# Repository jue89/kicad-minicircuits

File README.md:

# Evaluation boards for Mini-Circuits parts

Some parts from [Mini-Circuits®](http://www.minicircuits.com) brought onto two-sided PCBs with 1mm FR4 core and 35µm copper.

## Cloning

```
git clone --recursive https://github.com/jue89/kicad-minicircuits.git
cd kicad-minicircuits
./setup.sh
```

## Generating Gerber files

I found a little python script for plotting Gerber files in the KiCad repository (demos/python\_scripts\_examples). It will be called by the plot Bash script

```
./plot.sh
```

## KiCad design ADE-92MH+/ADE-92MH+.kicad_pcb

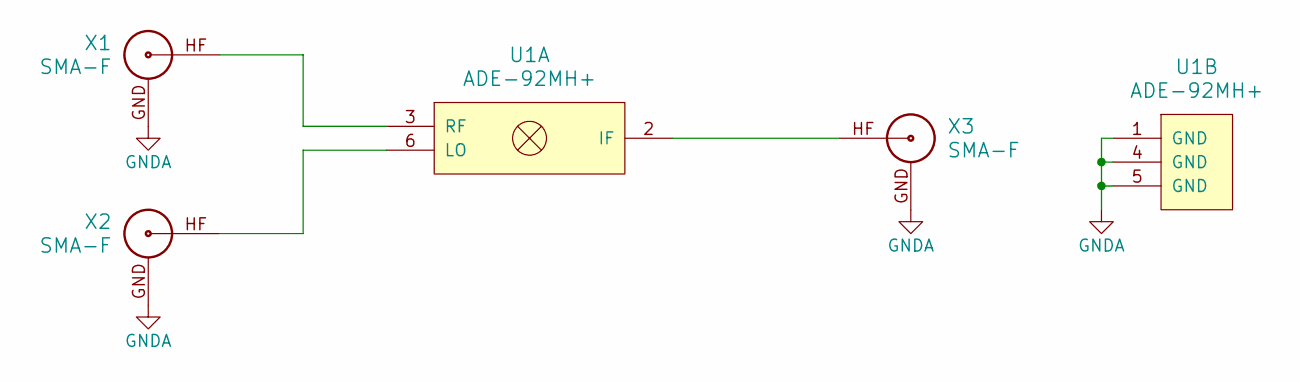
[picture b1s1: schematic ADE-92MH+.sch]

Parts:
U1: ADE-92MH+; CD636
X1, X2, X3: SMA-F; SMA-F-THT

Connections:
GNDA: U1.1 (GND), U1.4 (GND), U1.5 (GND), X1.GND, X2.GND, X3.GND
unnamed: U1.2 (IF), X3.HF
unnamed: U1.3 (RF), X1.HF
unnamed: U1.6 (LO), X2.HF

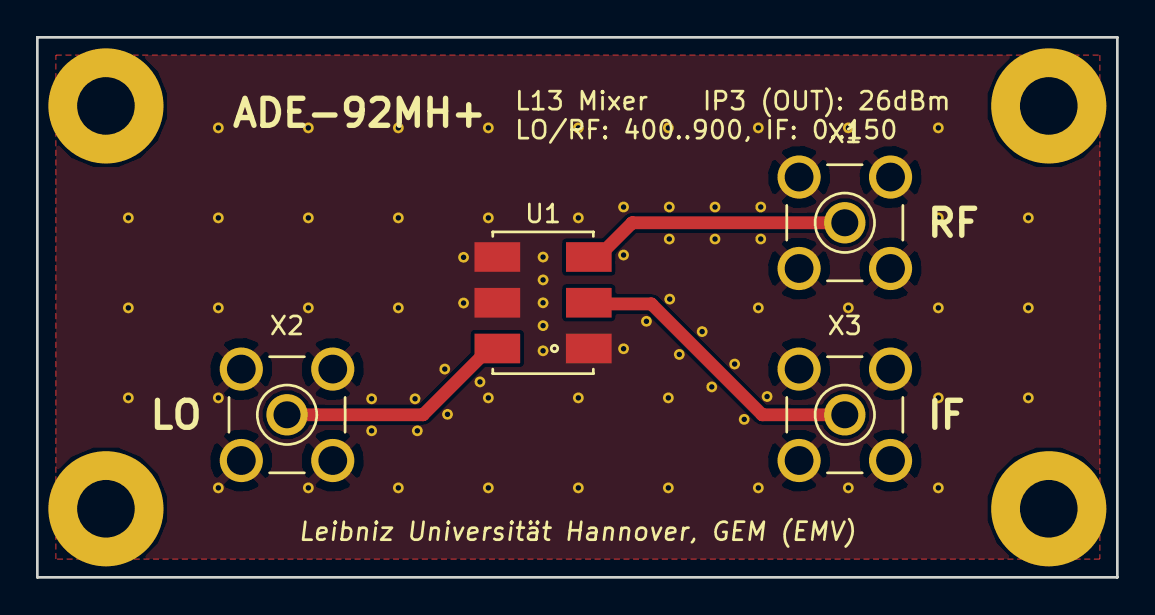
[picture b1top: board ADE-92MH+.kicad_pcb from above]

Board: 2 copper layers, 60.0 x 30.0 mm, 4 parts (0 on the bottom side), 4 nets.

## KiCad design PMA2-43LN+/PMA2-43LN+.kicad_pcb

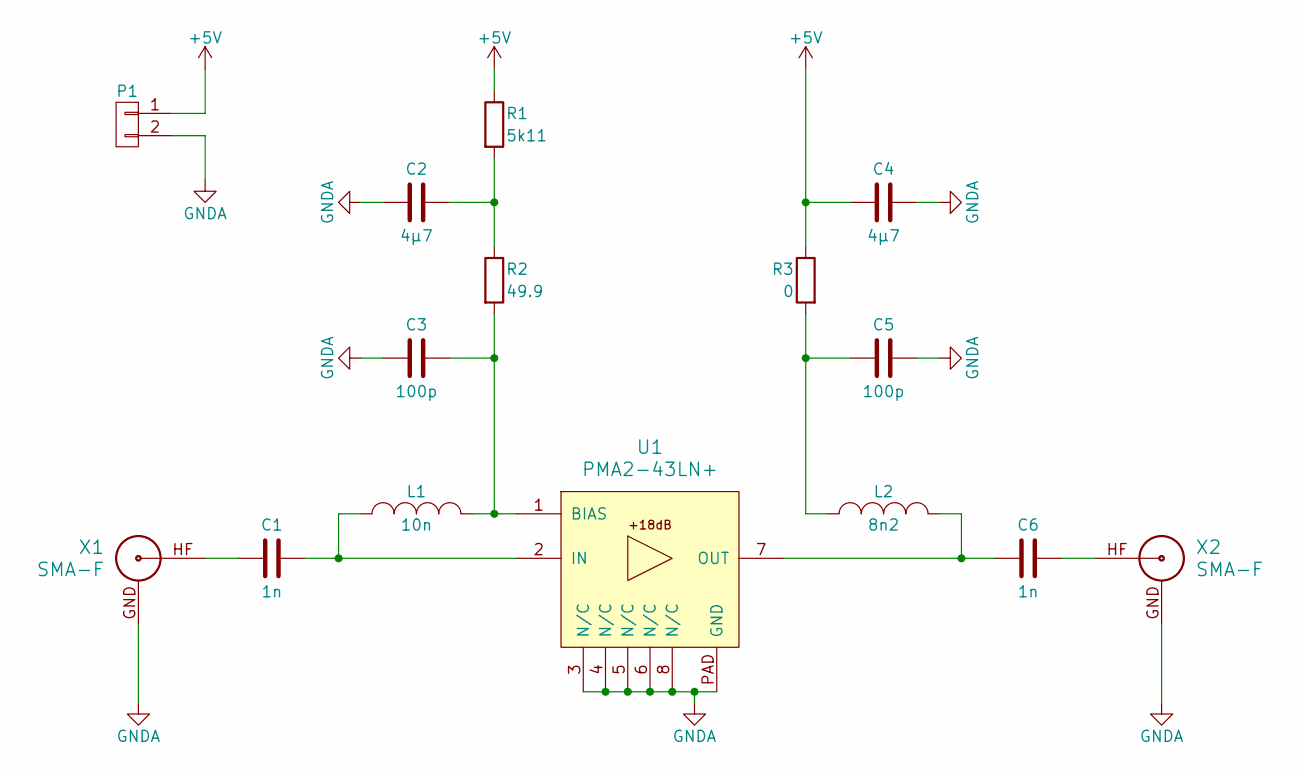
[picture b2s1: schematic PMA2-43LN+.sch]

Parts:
C1, C6: 1n; C_0805
C2, C4: 4µ7; C_0805
C3, C5: 100p; C_0805
L1: 10n; Neosid_Inductor_SM-NE29_SMD1008
L2: 8n2; Neosid_Inductor_SM-NE29_SMD1008
P1: CONN_01X02; Pin_Header_Straight_1x02
R1: 5k11; R_0805
R2: 49.9; R_0805
R3: 0; R_0805
U1: PMA2-43LN+; MC1631
X1, X2: SMA-F; SMA-F-THT

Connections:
+5V: C4.2, P1.1, R1.1, R3.1
GNDA: C2.2, C3.2, C4.1, C5.1, P1.2, U1.3 (N/C), U1.4 (N/C), U1.5 (N/C), U1.6 (N/C), U1.8 (N/C), U1.PAD (GND), X1.GND, X2.GND
unnamed: C1.1, L1.1, U1.2 (IN)
unnamed: C1.2, X1.HF
unnamed: C2.1, R1.2, R2.1
unnamed: C3.1, L1.2, R2.2, U1.1 (BIAS)
unnamed: C5.2, L2.1, R3.2
unnamed: C6.1, X2.HF
unnamed: C6.2, L2.2, U1.7 (OUT)

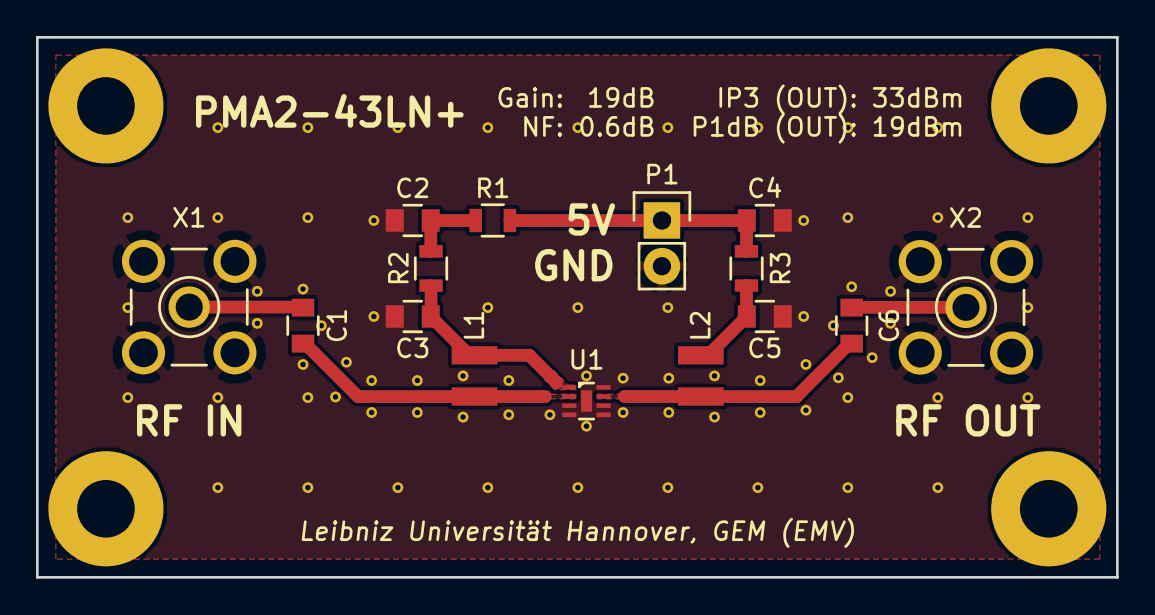
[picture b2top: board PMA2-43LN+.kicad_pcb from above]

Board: 2 copper layers, 60.0 x 30.0 mm, 15 parts (0 on the bottom side), 9 nets.

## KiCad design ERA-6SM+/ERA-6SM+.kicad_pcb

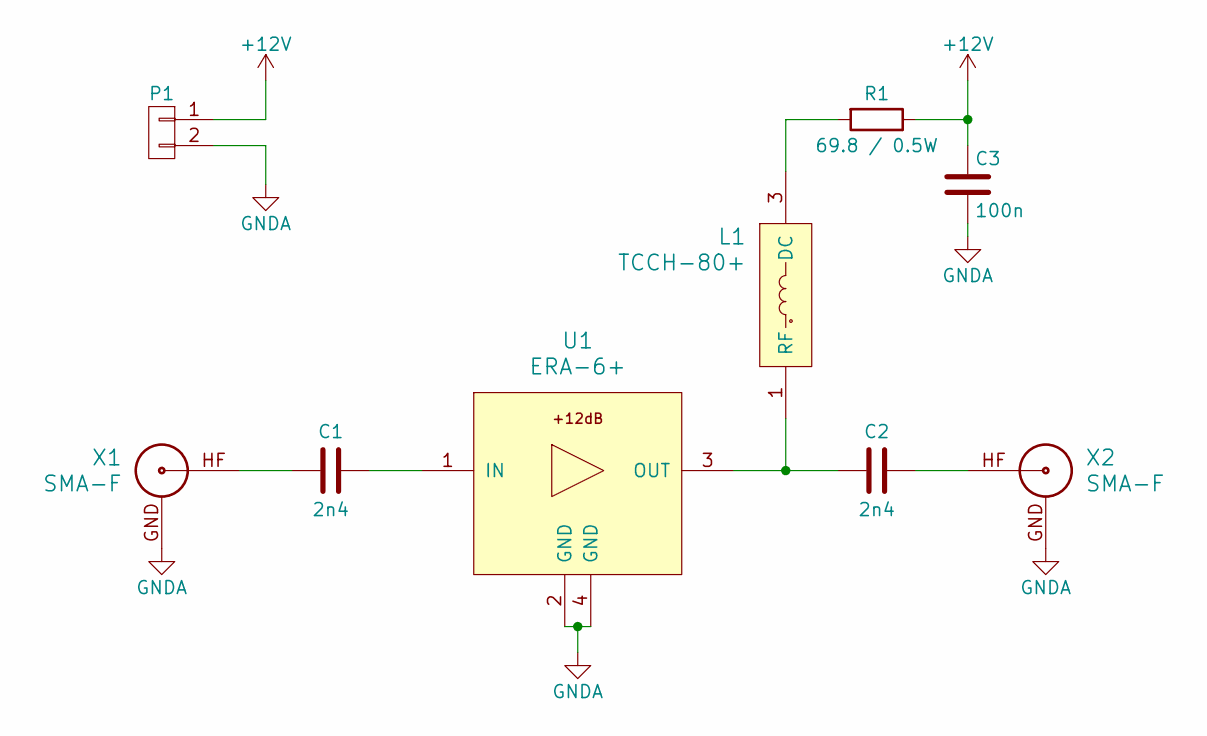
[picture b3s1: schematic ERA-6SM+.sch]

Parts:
C1, C2: 2n4; C_0805
C3: 100n; C_0805
L1: TCCH-80+; GU1604
P1: CONN_01X02; Pin_Header_Straight_1x02
R1: 69.8 / 0.5W; R_1206
U1: ERA-6+; WW107
X1, X2: SMA-F; SMA-F-THT

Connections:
+12V: C3.1, P1.1, R1.1
GNDA: C3.2, P1.2, U1.2 (GND), U1.4 (GND), X1.GND, X2.GND
unnamed: C1.1, U1.1 (IN)
unnamed: C1.2, X1.HF
unnamed: C2.1, X2.HF
unnamed: C2.2, L1.1 (RF), U1.3 (OUT)
unnamed: L1.3 (DC), R1.2

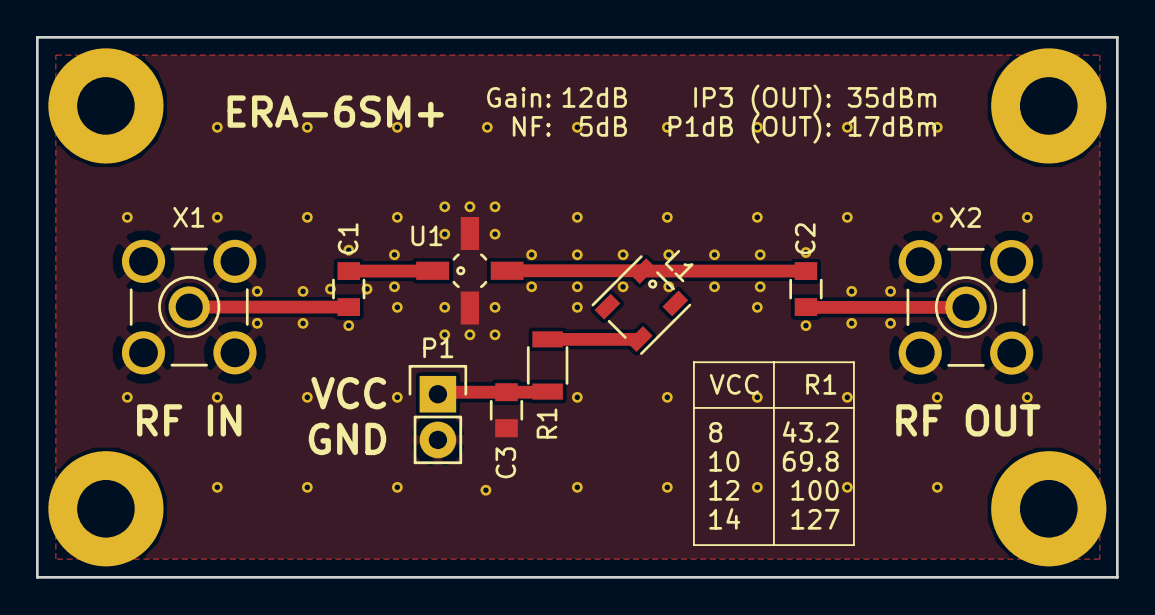
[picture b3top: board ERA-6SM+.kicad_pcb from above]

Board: 2 copper layers, 60.0 x 30.0 mm, 9 parts (0 on the bottom side), 7 nets.

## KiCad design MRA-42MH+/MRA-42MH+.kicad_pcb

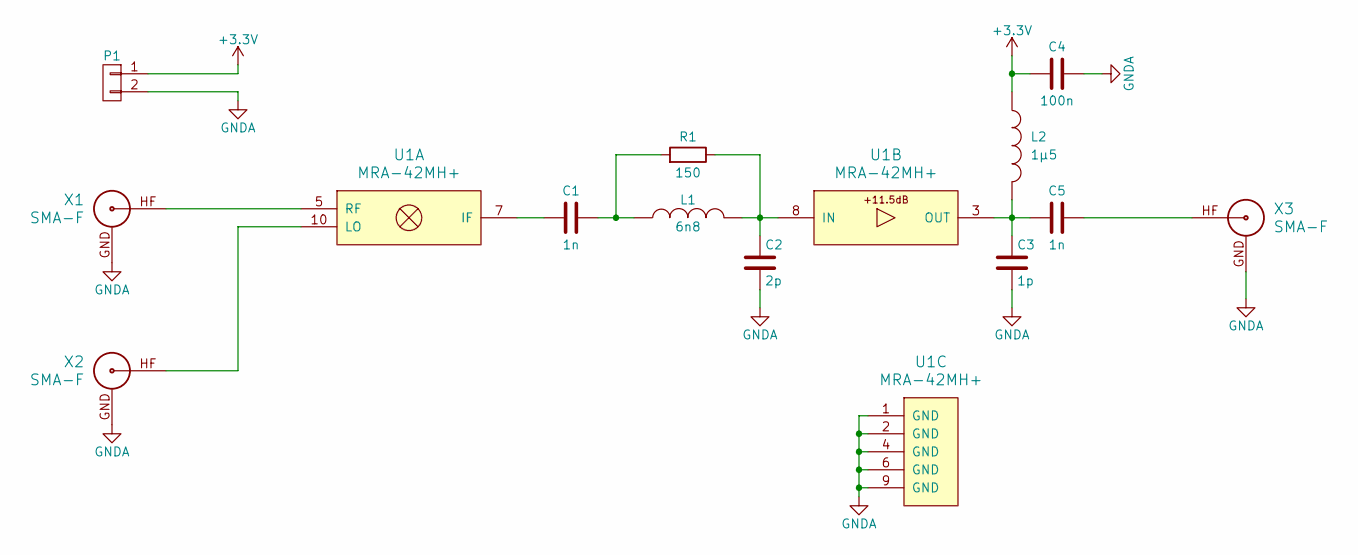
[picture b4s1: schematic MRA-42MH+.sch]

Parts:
C1, C5: 1n; C_0805
C2: 2p; C_0805
C3: 1p; C_0805
C4: 100n; C_0805
L1: 6n8; Neosid_Inductor_SM-NE29_SMD1008
L2: 1µ5; Neosid_Inductor_SM-NE29_SMD1008
P1: CONN_01X02; Pin_Header_Straight_1x02
R1: 150; R_0805
U1: MRA-42MH+; DZ1650
X1, X2, X3: SMA-F; SMA-F-THT

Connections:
+3V3: C4.2, L2.1, P1.1
GNDA: C2.2, C3.2, C4.1, P1.2, U1.1 (GND), U1.2 (GND), U1.4 (GND), U1.6 (GND), U1.9 (GND), X1.GND, X2.GND, X3.GND
unnamed: C1.1, L1.1, R1.2
unnamed: C1.2, U1.7 (IF)
unnamed: C2.1, L1.2, R1.1, U1.8 (IN)
unnamed: C3.1, C5.2, L2.2, U1.3 (OUT)
unnamed: C5.1, X3.HF
unnamed: U1.5 (RF), X1.HF
unnamed: U1.10 (LO), X2.HF

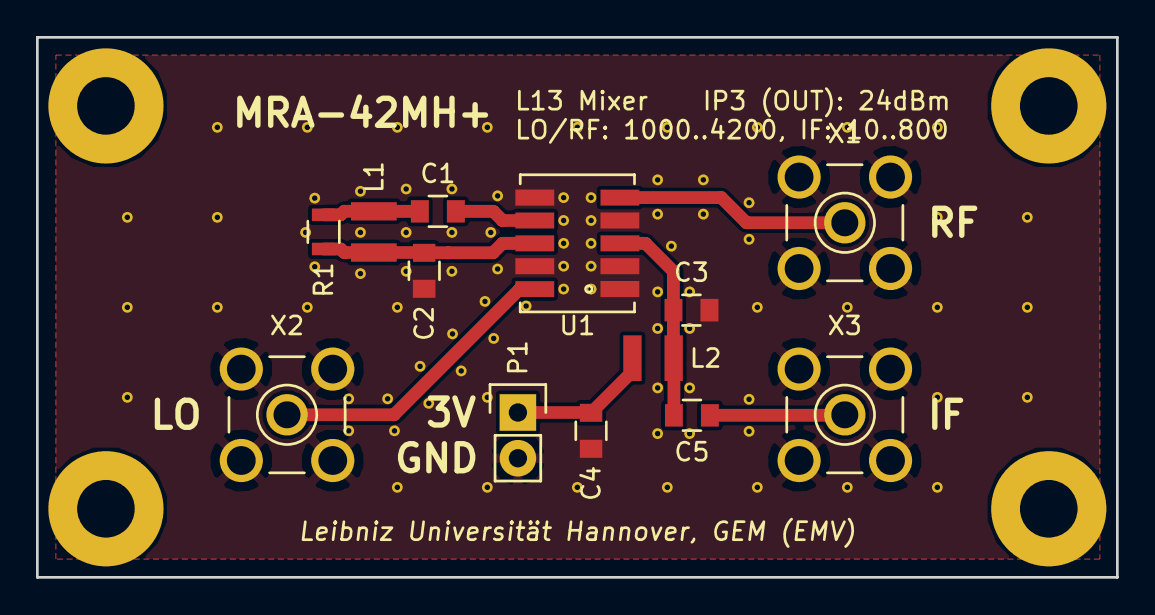
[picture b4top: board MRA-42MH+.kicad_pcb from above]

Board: 2 copper layers, 60.0 x 30.0 mm, 13 parts (0 on the bottom side), 9 nets.

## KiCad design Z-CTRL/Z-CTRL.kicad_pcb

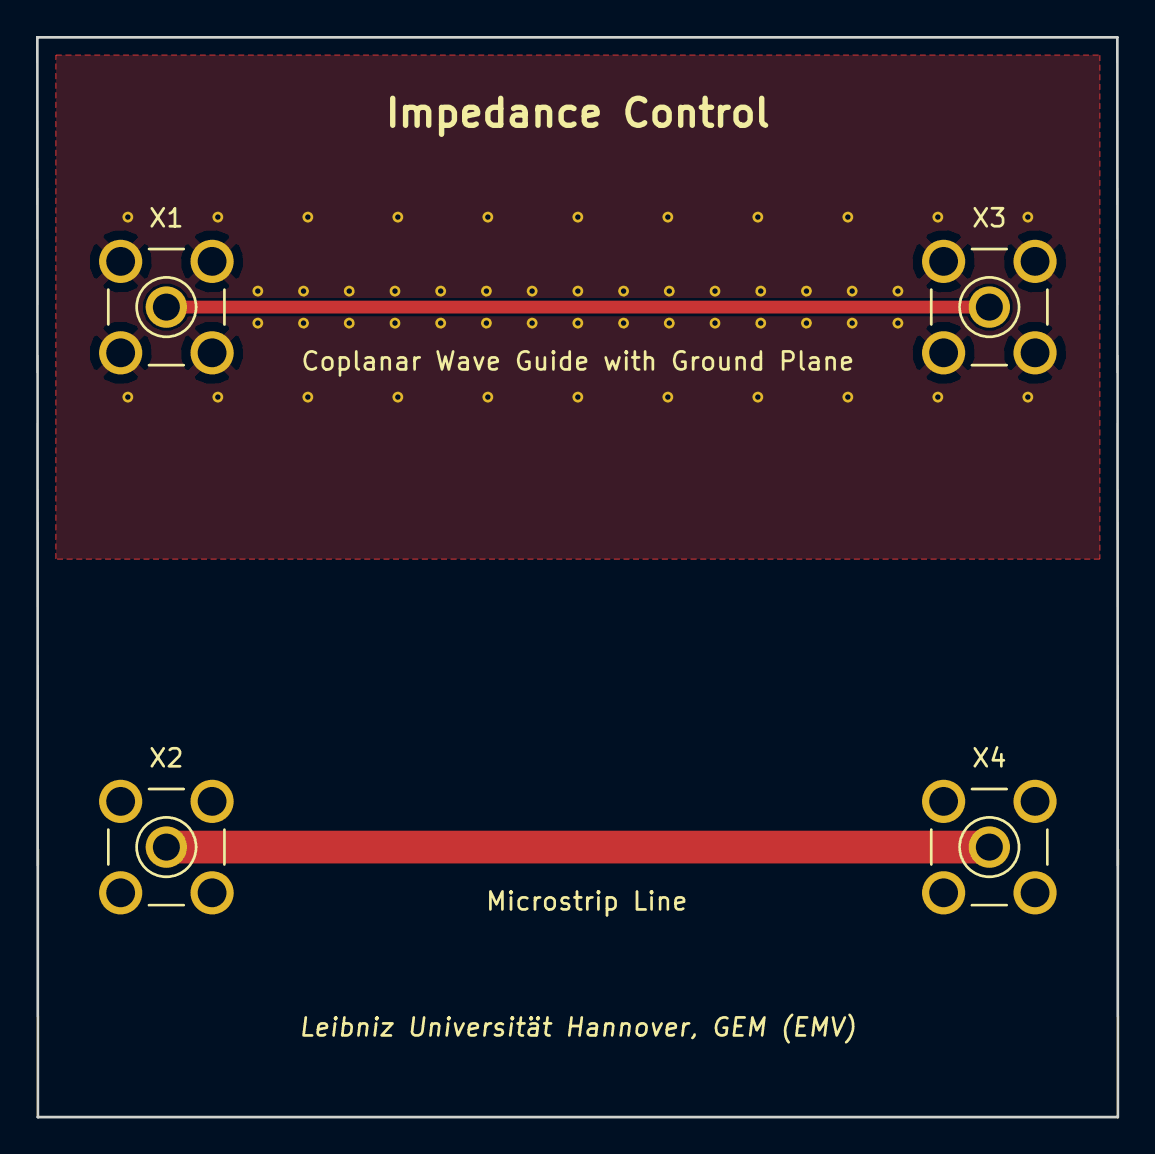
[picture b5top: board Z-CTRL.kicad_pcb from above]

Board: 2 copper layers, 60.0 x 60.0 mm, 4 parts (0 on the bottom side), 4 nets.

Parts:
X1, X2, X3, X4: SMA-F; SMA-F-THT

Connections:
unnamed: X1.GND, X3.GND
unnamed: X1.HF, X3.HF
unnamed: X2.GND, X4.GND
unnamed: X2.HF, X4.HF

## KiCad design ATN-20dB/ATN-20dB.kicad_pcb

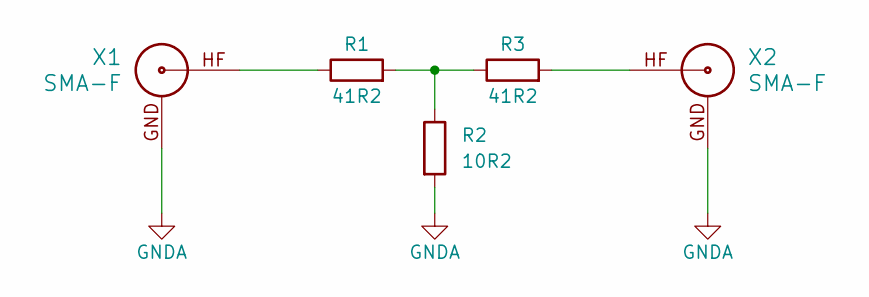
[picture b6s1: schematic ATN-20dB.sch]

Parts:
R1, R3: 41R2; R_0805
R2: 10R2; R_0805
X1, X2: SMA-F; SMA-F-THT

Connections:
GNDA: R2.2, X1.GND, X2.GND
unnamed: R1.1, X1.HF
unnamed: R1.2, R2.1, R3.1
unnamed: R3.2, X2.HF

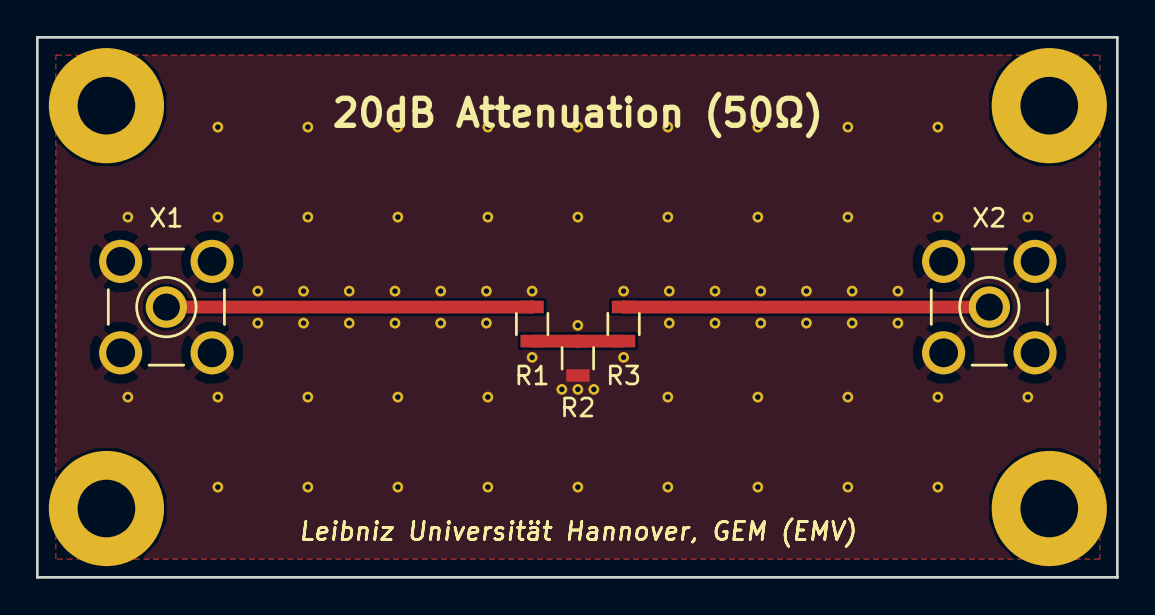
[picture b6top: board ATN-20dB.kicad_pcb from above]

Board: 2 copper layers, 60.0 x 30.0 mm, 5 parts (0 on the bottom side), 4 nets.

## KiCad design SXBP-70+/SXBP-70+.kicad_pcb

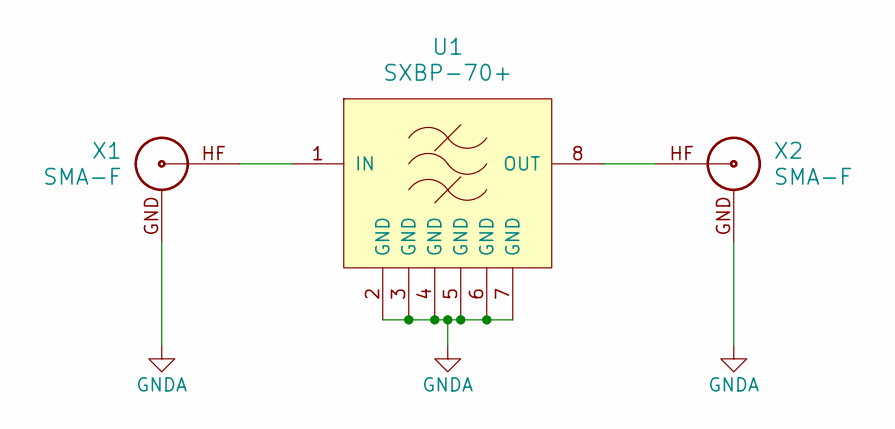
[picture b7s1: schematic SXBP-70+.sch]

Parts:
U1: SXBP-70+; HF1139
X1, X2: SMA-F; SMA-F-THT

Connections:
GNDA: U1.2 (GND), U1.3 (GND), U1.4 (GND), U1.5 (GND), U1.6 (GND), U1.7 (GND), X1.GND, X2.GND
unnamed: U1.1 (IN), X1.HF
unnamed: U1.8 (OUT), X2.HF

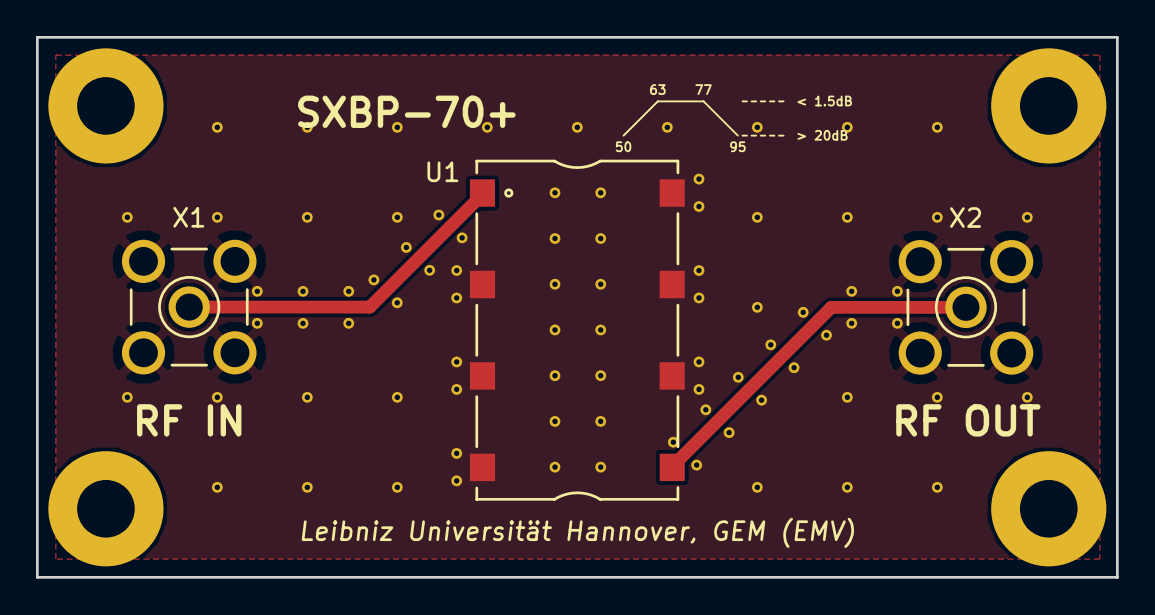
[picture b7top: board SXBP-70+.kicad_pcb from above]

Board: 2 copper layers, 60.0 x 30.0 mm, 3 parts (0 on the bottom side), 3 nets.

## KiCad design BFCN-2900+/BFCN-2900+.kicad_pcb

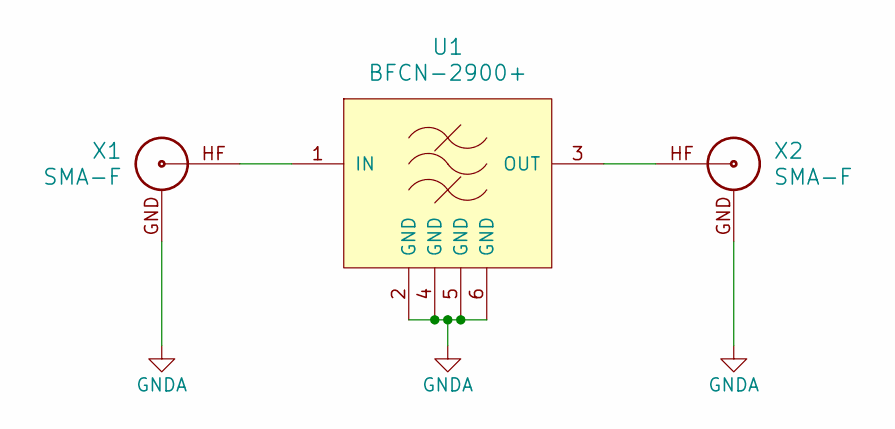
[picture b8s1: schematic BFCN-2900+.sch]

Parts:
U1: BFCN-2900+; FV1206-1
X1, X2: SMA-F; SMA-F-THT

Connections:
GNDA: U1.2 (GND), U1.4 (GND), U1.5 (GND), U1.6 (GND), X1.GND, X2.GND
unnamed: U1.1 (IN), X1.HF
unnamed: U1.3 (OUT), X2.HF

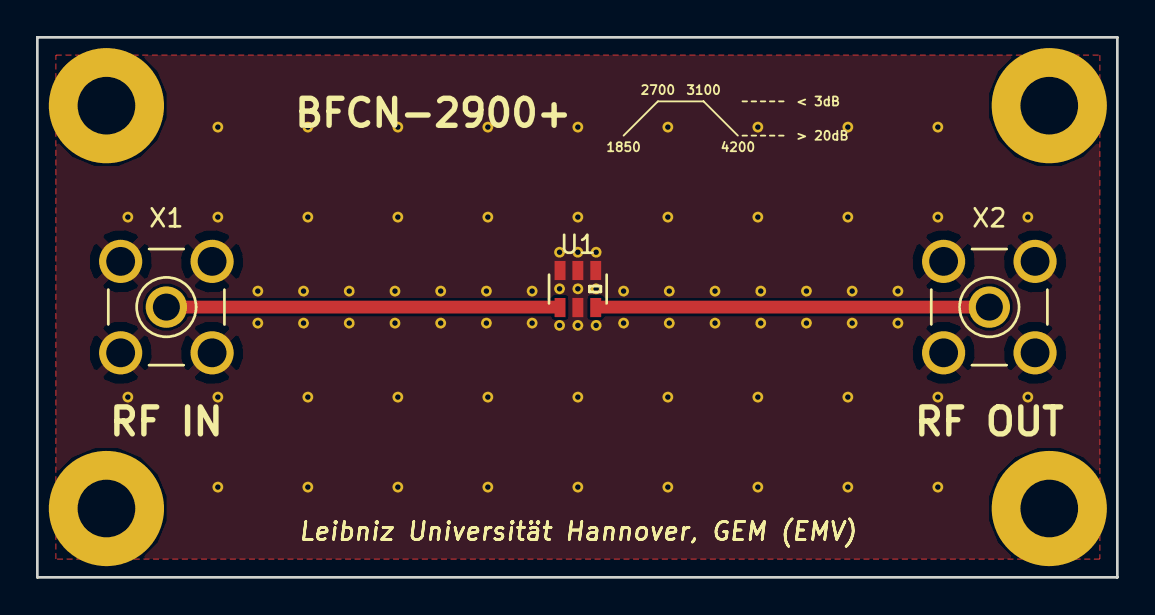
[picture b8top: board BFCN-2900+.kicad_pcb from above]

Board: 2 copper layers, 60.0 x 30.0 mm, 3 parts (0 on the bottom side), 3 nets.

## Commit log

2016-06-03 Ignore temporary files
2016-06-03 BFCN-2900+
2016-06-03 BFCN-2900+: Removed thermals
2016-06-03 BFCN-2900+: Some vias, new footprints
2016-06-03 SXBP-640+
2016-06-03 SXBP-70+
2016-06-06 BFCN-2900+: Added some vias
2016-06-06 Ignoring Gerber files
2016-06-06 BFCN-2900+: Moved U1
2016-06-06 MRA-42MH+
2016-06-07 Removed some missplaced vias
2016-06-07 ADE-92MH+
2016-06-13 BFCN-2900+: corrected 50Ohm CPW, new VIA arrangement
2016-06-13 BFCN-640+: corrected 50Ohm CPW, new VIA arrangement
2016-06-13 BFCN-70+: corrected 50Ohm CPW, new VIA arrangement
2016-06-15 MRA-42MH+: corrected 50Ohm CPW, new VIA arrangement
2016-06-15 ADE-92MH+: corrected 50Ohm CPW, new VIA arrangement
2016-06-15 ERA-6SM+
2016-06-15 Removed all absolut paths and libraries
    All required external libraries are now added by GIT submodules.
2016-06-15 Added helper script to setup footprint module paths
    Since KiCAD is not able to work with relative paths, we need this script ...
2016-06-16 PMA2-43LN+: First draft
2016-06-16 PMA2-43LN+: Finalised
2016-06-16 ATN-6dB
2016-06-16 ATN-10dB
2016-06-16 ATN-20dB
2016-06-17 ERA-6SM+: Changed from 12V supply to 10V
2016-06-17 Batch plot to Gerber files
2016-06-20 ERA-6SM+: Table for bias resistor selection
2016-06-27 Z-CTRL
2016-06-28 z-CTRL: Typo on silk screen
2016-06-28 ERA-6SM+: Corrected RF choke
2016-06-28 Updated kicad-lib-minicircuits
2016-06-28 MRA-42MH+: Updated layout according Testboard
2016-06-28 Updated plot script
2016-06-29 Added some thermals to THT parts
